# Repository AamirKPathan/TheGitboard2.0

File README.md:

# GitBoard 2.0

## Project Description
GitBoard 2.0 is an **8‑key Git‑focused macropad** powered by the **Seeeduino XIAO RP2040**.  
It automates common Git commands using **CircuitPython** or **QMK**, making version control faster and more intuitive.

The board uses a **2×4 layout**, **direct‑wired switches**, and a custom PCB designed in **KiCad**.  
Each key triggers a Git command such as `git status`, `git add .`, or `git commit -m ""`.

---

# 📸 Required Images

## 1. Macropad Render

## 2. Schematic Screenshot

## 3. PCB Layout Screenshot

## 4. Case / 3D View Screenshot

---

## 🛠️ Hardware
- Microcontroller: Seeeduino XIAO (RP2040)
- Switches: 8 × momentary push buttons
- Layout: 2 rows × 4 columns
- Wiring: Direct pins (D0–D7)
- Connection: USB‑C
- Power: 5 V from USB
- Design Software: KiCad 7.x

---

## 💻 CircuitPython Firmware Example

```python
import board, digitalio, usb_hid
from adafruit_hid.keyboard import Keyboard

kbd = Keyboard(usb_hid.devices)

pins = [board.D0, board.D1, board.D2, board.D3, board.D4, board.D5, board.D6, board.D7]
commands = [
    "git status\n",
    "git add .\n",
    "git commit -m \"\"\n",
    "git push\n",
    "git pull\n",
    "git checkout -b newbranch\n",
    "git merge main\n",
    "git log --oneline\n"
]

switches = [digitalio.DigitalInOut(pin) for pin in pins]
for sw in switches:
    sw.direction = digitalio.Direction.INPUT
    sw.pull = digitalio.Pull.UP

while True:
    for i, sw in enumerate(switches):
        if not sw.value:
            kbd.send_string(commands[i])
```

---

## ⚙️ QMK Firmware
The QMK firmware for this board is located in the `firmware/` folder.

### Matrix Layout
Direct‑wired 2×4 matrix:

```
Row 0 → D0, D1, D2, D3  
Row 1 → D4, D5, D6, D7
```

---

## 📦 Bill of Materials (BOM)

| Item | Quantity | Description | Footprint |
|------|----------|-------------|-----------|
| Seeeduino XIAO | 1 | Microcontroller | MODULE‑SEEEDUINO‑XIAO |
| Tactile Switch | 8 | Momentary push button | SW_Push |
| Custom PCB | 1 | Designed in KiCad | — |
| USB‑C Cable | 1 | Power + data | — |
| Solder | — | Assembly | — |
| Keycaps | 8 | For labeling | — |
| Case | 1 | 3D printed enclosure | — |
| Screws | 4 | M3×16 | — |

---

## 🧰 License
MIT License

---

## 🚀 Future Ideas
- RGB LEDs  
- OLED display  
- QMK layers  
- Custom keycaps  
- Encoder support  
- Hotswap sockets

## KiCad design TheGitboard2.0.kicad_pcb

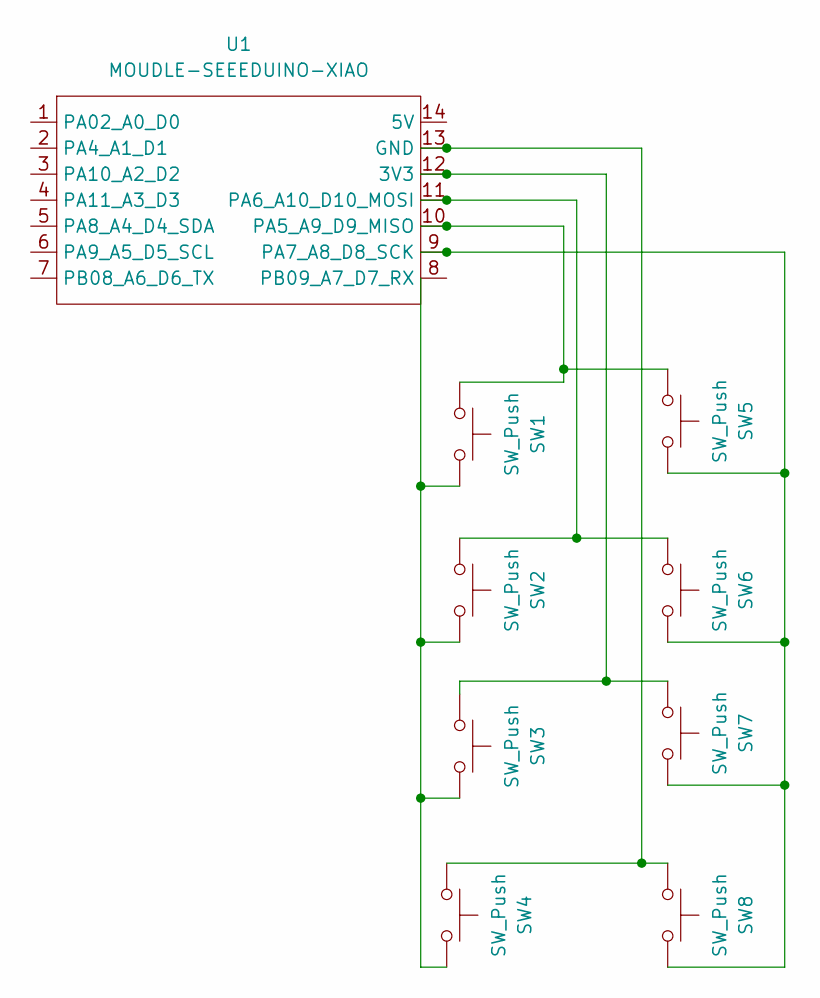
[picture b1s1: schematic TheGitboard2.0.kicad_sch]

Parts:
SW1, SW2, SW3, SW4, SW5, SW6, SW7, SW8: SW_Push; SW_Cherry_MX_1.00u_PCB
U1: MOUDLE-SEEEDUINO-XIAO; XIAO-Generic-Hybrid-14P-2.54-21X17.8MM

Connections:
unnamed: SW1.2, SW2.2, SW3.2, SW4.2
unnamed: SW3.1, SW7.1, U1.12 (3V3)
unnamed: SW4.1, SW8.1, U1.13 (GND)
unnamed: SW1.1, SW5.1, U1.10 (PA5_A9_D9_MISO)
unnamed: SW2.1, SW6.1, U1.11 (PA6_A10_D10_MOSI)
unnamed: SW5.2, SW6.2, SW7.2, SW8.2, U1.9 (PA7_A8_D8_SCK)

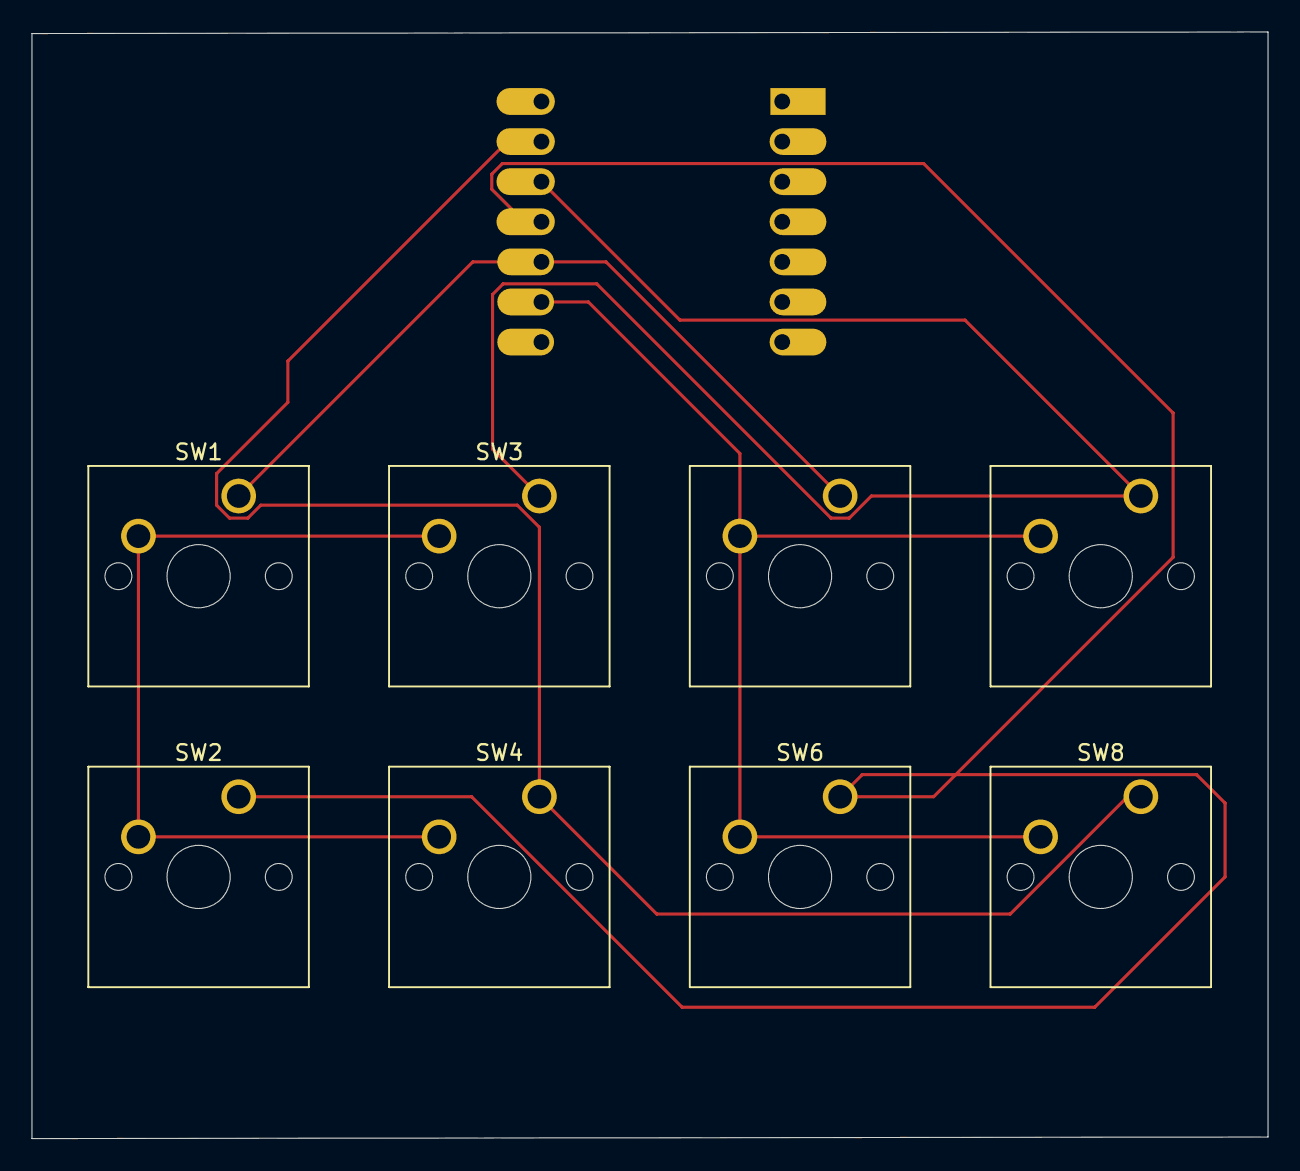
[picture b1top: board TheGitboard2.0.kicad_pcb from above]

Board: 2 copper layers, 78.3 x 70.1 mm, 9 parts (1 on the bottom side), 6 nets.

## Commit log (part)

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2026-06-15 Add updated README and project files
2026-06-28 Jun 28, 2026, 11:16 AM
2026-06-28 Jun 28, 2026, 11:18 AM
2026-06-28 Jun 28, 2026, 11:27 AM
